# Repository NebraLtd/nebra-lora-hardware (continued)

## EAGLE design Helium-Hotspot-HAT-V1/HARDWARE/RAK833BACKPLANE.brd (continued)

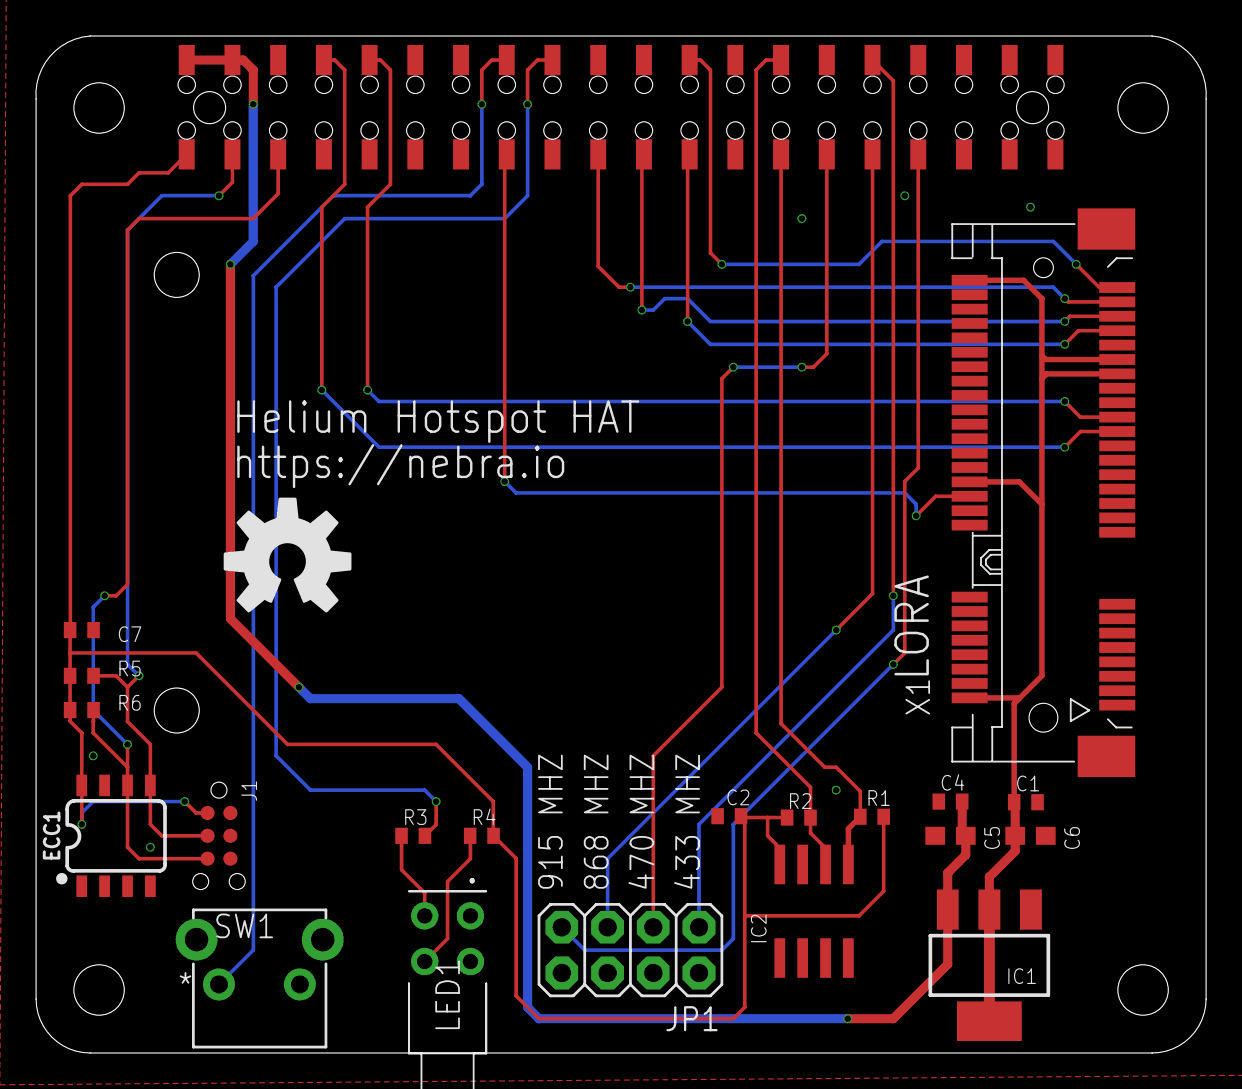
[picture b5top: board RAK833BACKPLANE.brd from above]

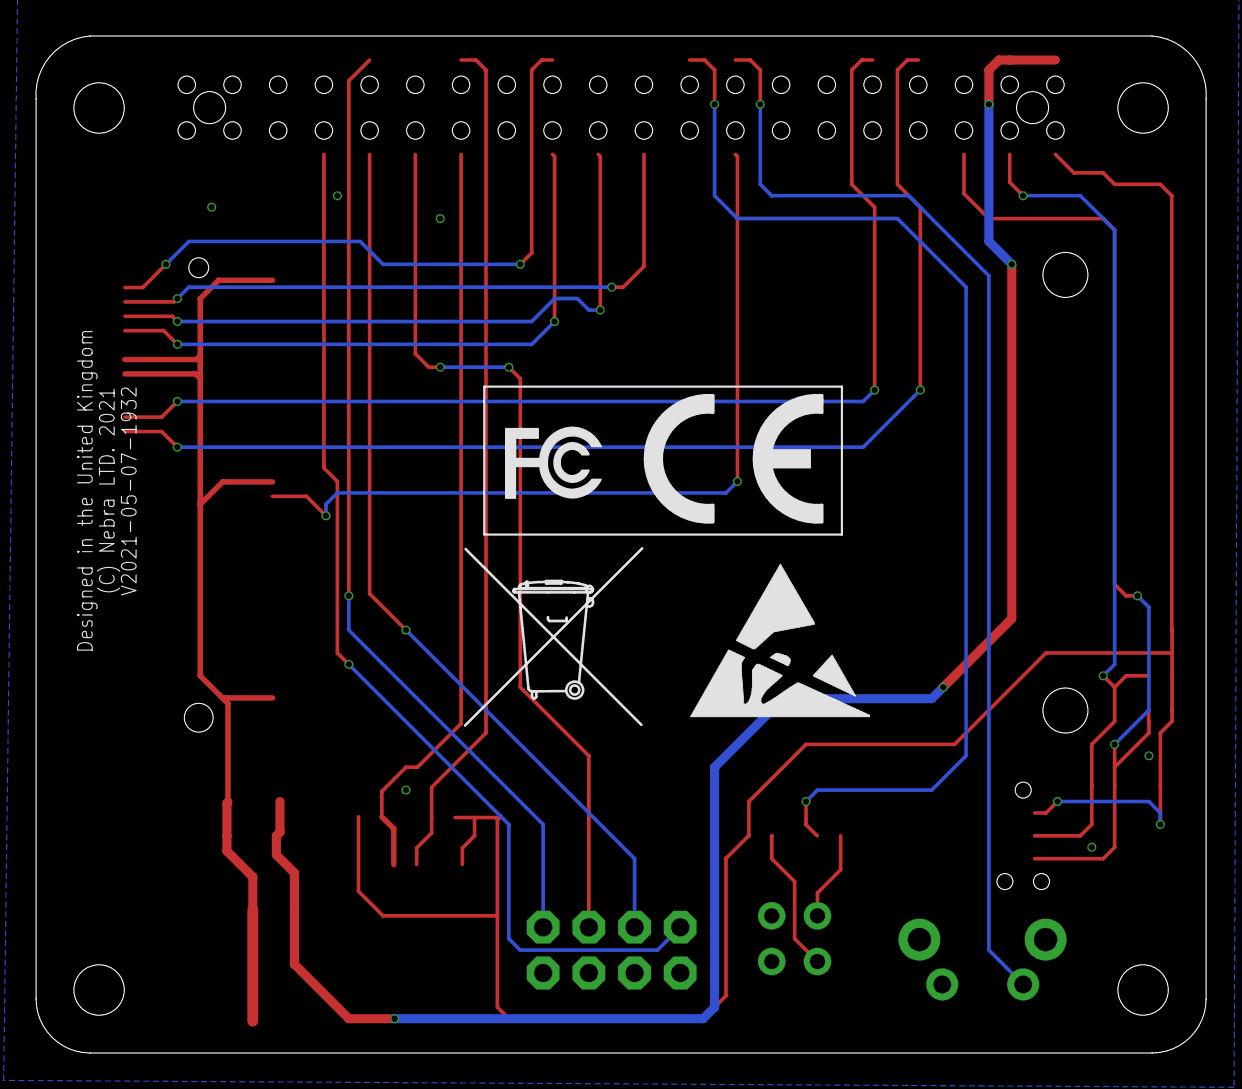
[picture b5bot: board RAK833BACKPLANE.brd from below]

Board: 2 copper layers, 65.0 x 56.5 mm, 26 parts (4 on the bottom side), 23 nets.

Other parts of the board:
U$1: TONNE_10.00
U$3: ESD_10.00
U$4: CE_7.3MM
U$5: FCC_20X8.35MM
U$6: OSHW-LOGO-L

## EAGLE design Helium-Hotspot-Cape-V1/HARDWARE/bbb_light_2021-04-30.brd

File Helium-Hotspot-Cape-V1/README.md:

# Nebra Light Hotspot Beaglebone Black Cape

The Nebra Helium Hotspot BBB Cape is designed for the new generation of helium Light Hotspots.

It features space for the Radio Module, a button & two LEDs. Along with an EEPROM to store Beaglebone Cape data and a ATECC to comply with Helium Hotspot Requirements.

# DIY Note

Please note, while you are able to build a DIY option of this board it will not earn HNT unless the ECC is programmed by an authorised Helium Maker.

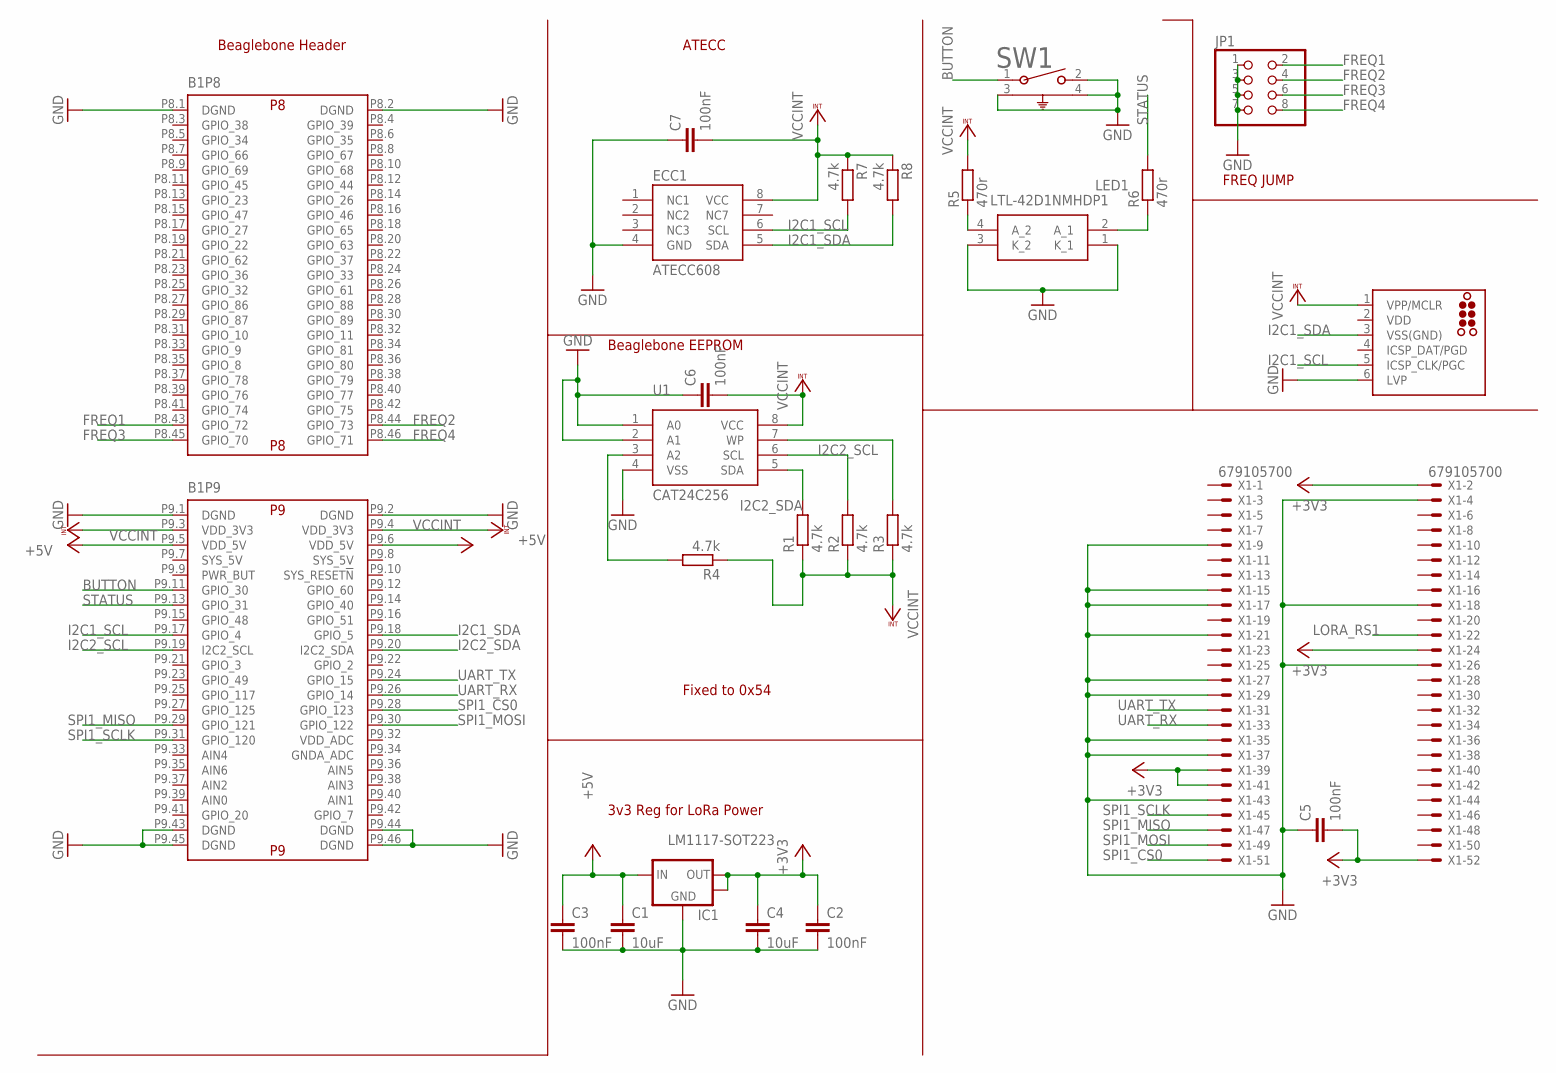
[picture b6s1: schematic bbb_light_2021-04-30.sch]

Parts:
B1: SPARKFUN_BEAGLE_BONE_BLACK_CAPE; BEAGLE_BONE_BLACK_CAPE
C1, C4: 10uF; C0603
C2, C3, C5, C6, C7: 100nF; C0603
ECC1: ATECC608; SO08
IC1: LM1117-SOT223; SOT-223-3
J1: TC2030-MCP-NL
JP1: PINHD-2X4; 2X04
LED1: LTL-42D1NMHDP1; LTL42D1NMHDP1
R1, R2, R3, R4, R7, R8: 4.7k; R0603
R5, R6: 470r; R0603
SW1: 1825027-8; SW2_1825027-C_TEC
U1: CAT24C256; SOIC8
X1: 679105700

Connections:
+3V3: C2.1, C4.1, C5.2, IC1.2 (VOUT), IC1.4 (HEATSINK), X1.2, X1.24, X1.39, X1.41, X1.52
+5V: B1.P9.5 (VDD_5V), B1.P9.6 (VDD_5V), C1.1, C3.1, IC1.3 (VIN)
BUTTON: B1.P9.11 (GPIO_30), SW1.1
FREQ1: B1.P8.43 (GPIO_72), JP1.2
FREQ2: B1.P8.44 (GPIO_73), JP1.4
FREQ3: B1.P8.45 (GPIO_70), JP1.6
FREQ4: B1.P8.46 (GPIO_71), JP1.8
GND: B1.P8.1 (DGND), B1.P8.2 (DGND), B1.P9.1 (DGND), B1.P9.2 (DGND), B1.P9.43 (DGND), B1.P9.44 (DGND), B1.P9.45 (DGND), B1.P9.46 (DGND), C1.2, C2.2, C3.2, C4.2, C5.1, C6.1, C7.1, ECC1.4 (GND), IC1.1 (GND), J1.6 (LVP), JP1.1, JP1.3, JP1.5, JP1.7, LED1.1 (K_1), LED1.3 (K_2), SW1.2, SW1.3, SW1.4, U1.1 (A0), U1.2 (A1), U1.4 (VSS), X1.4, X1.9, X1.15, X1.17, X1.18, X1.21, X1.26, X1.27, X1.29, X1.35, X1.37, X1.43
I2C1_SCL: B1.P9.17 (GPIO_4), ECC1.6 (SCL), J1.5 (ICSP_CLK/PGC), R7.2
I2C1_SDA: B1.P9.18 (GPIO_5), ECC1.5 (SDA), J1.3 (VSS(GND)), R8.2
I2C2_SCL: B1.P9.19 (I2C2_SCL), R2.2, U1.6 (SCL)
I2C2_SDA: B1.P9.20 (I2C2_SDA), R1.2, U1.5 (SDA)
LORA_RS1: X1.22
unnamed: R3.2, U1.7 (WP)
unnamed: R4.2, U1.3 (A2)
unnamed: LED1.4 (A_2), R5.1
unnamed: LED1.2 (A_1), R6.1
SPI1_CS0: B1.P9.28 (GPIO_123), X1.51
SPI1_MISO: B1.P9.29 (GPIO_121), X1.47
SPI1_MOSI: B1.P9.30 (GPIO_122), X1.49
SPI1_SCLK: B1.P9.31 (GPIO_120), X1.45
STATUS: B1.P9.13 (GPIO_31), R6.2
UART_RX: B1.P9.26 (GPIO_14), X1.33
UART_TX: B1.P9.24 (GPIO_15), X1.31
VCCINT: B1.P9.3 (VDD_3V3), B1.P9.4 (VDD_3V3), C6.2, C7.2, ECC1.8 (VCC), J1.1 (VPP/MCLR), R1.1, R2.1, R3.1, R4.1, R5.2, R7.1, R8.1, U1.8 (VCC)
VDD: J1.2 (VDD)

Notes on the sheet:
3v3 Reg for LoRa Power
Beaglebone Header
Beaglebone EEPROM
Fixed to 0x54
ATECC
FREQ JUMP

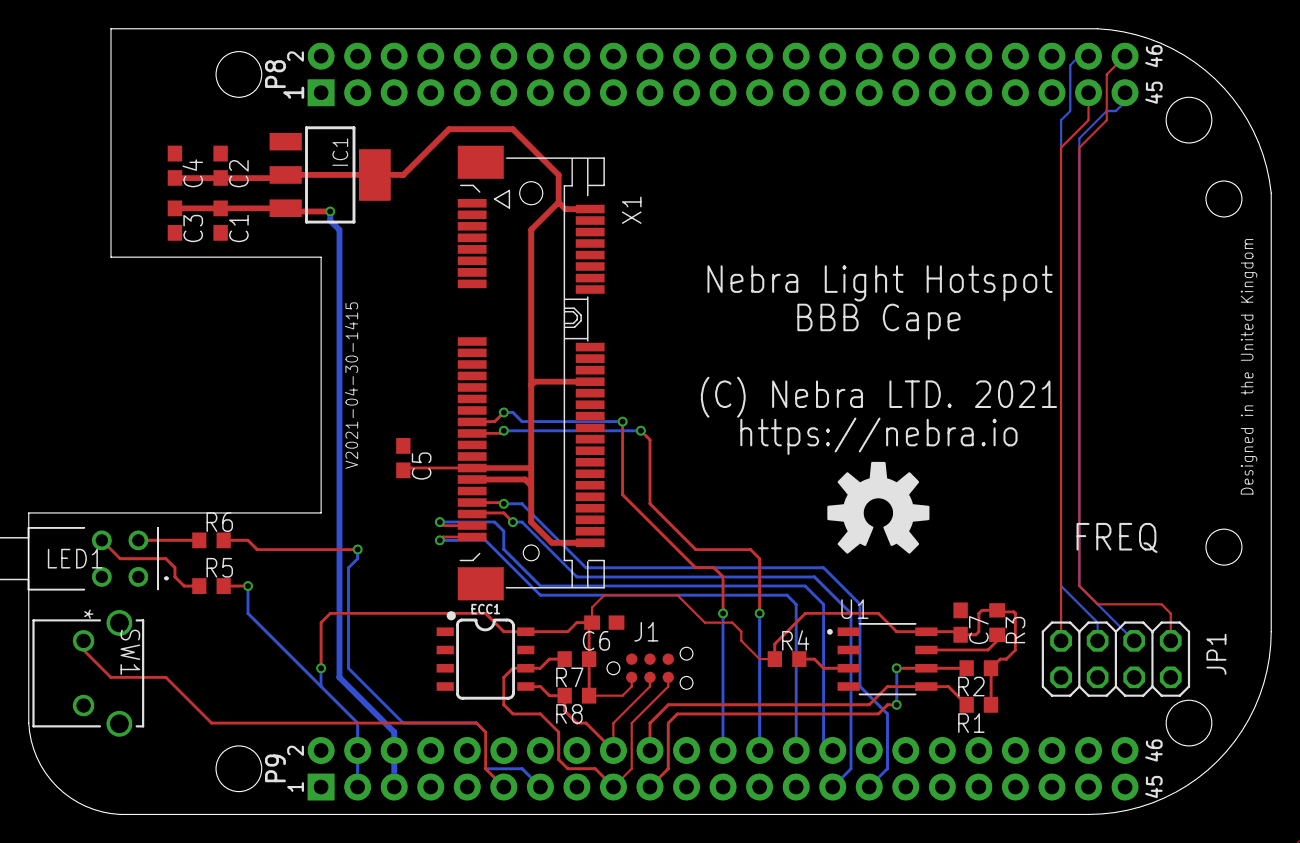
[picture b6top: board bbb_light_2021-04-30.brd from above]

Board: 2 copper layers, 86.4 x 54.6 mm, 25 parts (0 on the bottom side), 24 nets.

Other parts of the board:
U$1: OSHW-LOGO-L

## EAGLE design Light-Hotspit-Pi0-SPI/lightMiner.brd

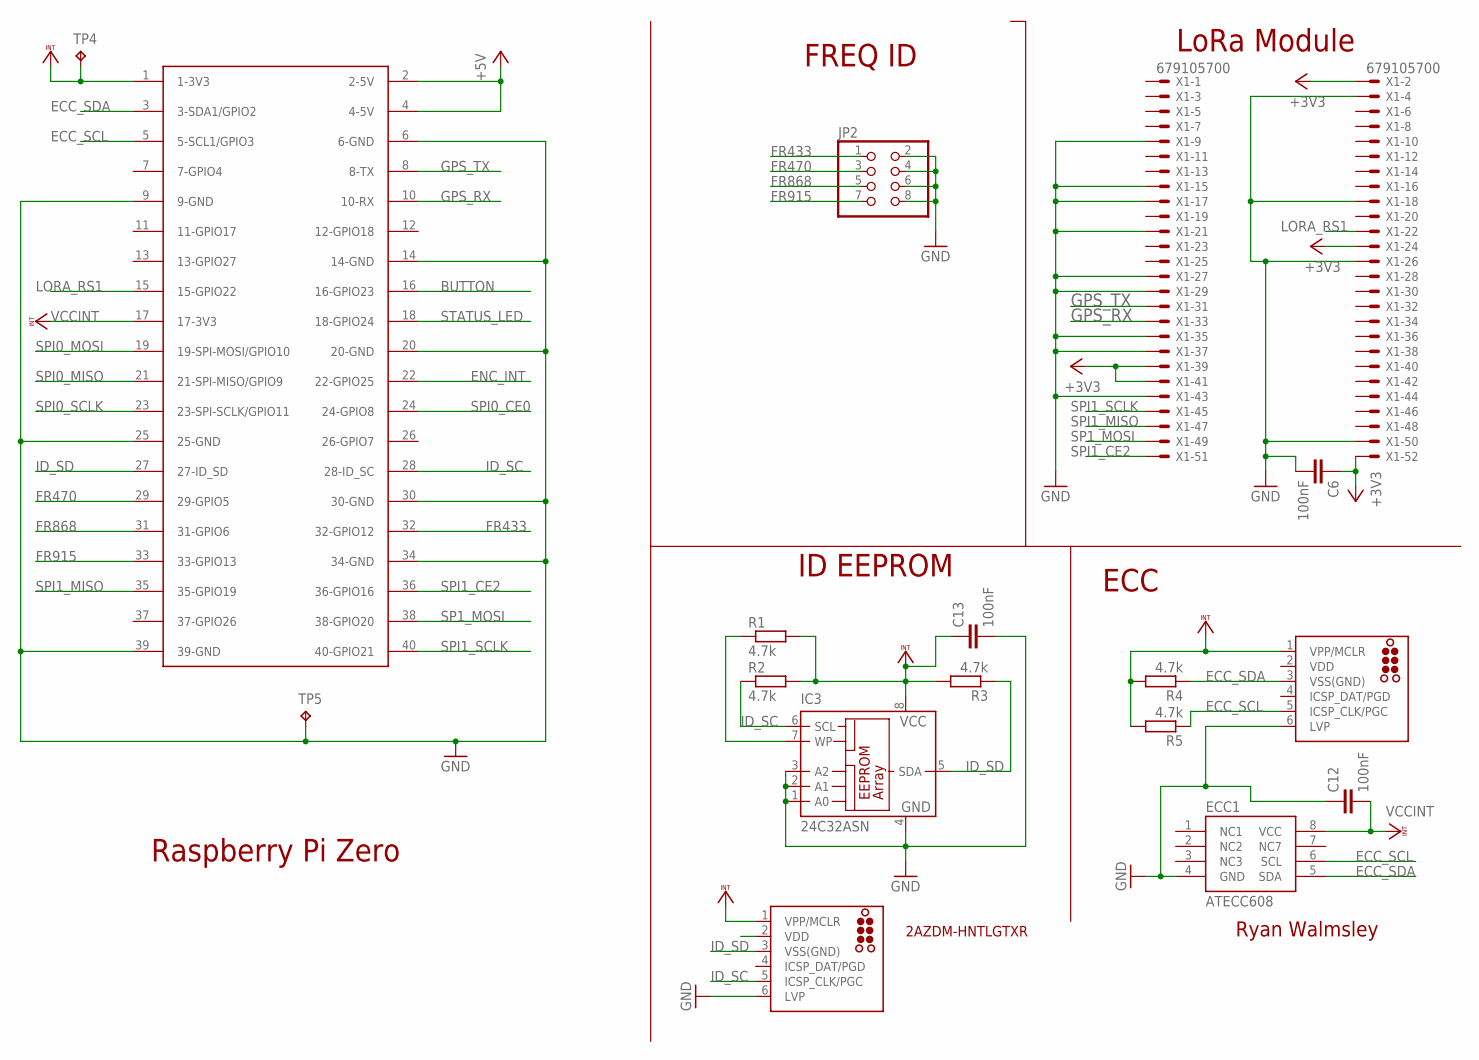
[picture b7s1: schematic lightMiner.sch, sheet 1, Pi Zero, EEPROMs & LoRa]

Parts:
C6, C12, C13: 100nF; C0603
ECC1: ATECC608; SO08
IC3: 24C32ASN; SO-08
J1, J3: TC2030-MCP-NL
JP2: PINHD-2X4; 2X04
R1, R2, R3, R4, R5: 4.7k; R0603
TP4, TP5: TPPAD1-13; P1-13
U$1: RASPBERRY-PI+PIZERO; RASPBERRY-PI-ZERO
X1: 679105700

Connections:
+3V3: C6.1, X1.2, X1.24, X1.39, X1.41, X1.52; also elsewhere on the board
+5V: U$1.2 (2-5V), U$1.4 (4-5V); also elsewhere on the board
BUTTON: U$1.16 (16-GPIO23); also elsewhere on the board
ECC_SCL: ECC1.6 (SCL), J1.5 (ICSP_CLK/PGC), R5.1, U$1.5 (5-SCL1/GPIO3)
ECC_SDA: ECC1.5 (SDA), J1.3 (VSS(GND)), R4.1, U$1.3 (3-SDA1/GPIO2)
ENC_INT: U$1.22 (22-GPIO25); also elsewhere on the board
FR433: JP2.1, U$1.32 (32-GPIO12)
FR470: JP2.3, U$1.29 (29-GPIO5)
FR868: JP2.5, U$1.31 (31-GPIO6)
FR915: JP2.7, U$1.33 (33-GPIO13)
GND: C6.2, C12.1, C13.2, ECC1.4 (GND), IC3.1 (A0), IC3.2 (A1), IC3.3 (A2), IC3.4 (GND), J1.6 (LVP), J3.6 (LVP), JP2.2, JP2.4, JP2.6, JP2.8, TP5.TP, U$1.6 (6-GND), U$1.9 (9-GND), U$1.14 (14-GND), U$1.20 (20-GND), U$1.25 (25-GND), U$1.30 (30-GND), U$1.34 (34-GND), U$1.39 (39-GND), X1.4, X1.9, X1.15, X1.17, X1.18, X1.21, X1.26, X1.27, X1.29, X1.35, X1.37, X1.43, X1.50; also elsewhere on the board
GPS_RX: U$1.10 (10-RX), X1.33
GPS_TX: U$1.8 (8-TX), X1.31
ID_SC: IC3.6 (SCL), J3.5 (ICSP_CLK/PGC), R2.1, U$1.28 (28-ID_SC)
ID_SD: IC3.5 (SDA), J3.3 (VSS(GND)), R3.1, U$1.27 (27-ID_SD)
LORA_RS1: U$1.15 (15-GPIO22), X1.22
unnamed: IC3.7 (WP), R1.1
SP1_MOSI: U$1.38 (38-GPIO20), X1.49
SPI0_CE0: U$1.24 (24-GPIO8); also elsewhere on the board
SPI0_MISO: U$1.21 (21-SPI-MISO/GPIO9); also elsewhere on the board
SPI0_MOSI: U$1.19 (19-SPI-MOSI/GPIO10); also elsewhere on the board
SPI0_SCLK: U$1.23 (23-SPI-SCLK/GPIO11); also elsewhere on the board
SPI1_CE2: U$1.36 (36-GPIO16), X1.51
SPI1_MISO: U$1.35 (35-GPIO19), X1.47
SPI1_SCLK: U$1.40 (40-GPIO21), X1.45
STATUS_LED: U$1.18 (18-GPIO24); also elsewhere on the board
VCCINT: C12.2, C13.1, ECC1.8 (VCC), IC3.8 (VCC), J1.1 (VPP/MCLR), J3.1 (VPP/MCLR), R1.2, R2.2, R3.2, R4.2, R5.2, TP4.TP, U$1.1 (1-3V3), U$1.17 (17-3V3)
VDD: J1.2 (VDD)

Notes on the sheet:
Raspberry Pi Zero
LoRa Module
ID EEPROM
ECC
FREQ ID
Ryan Walmsley
2AZDM-HNTLGTXR

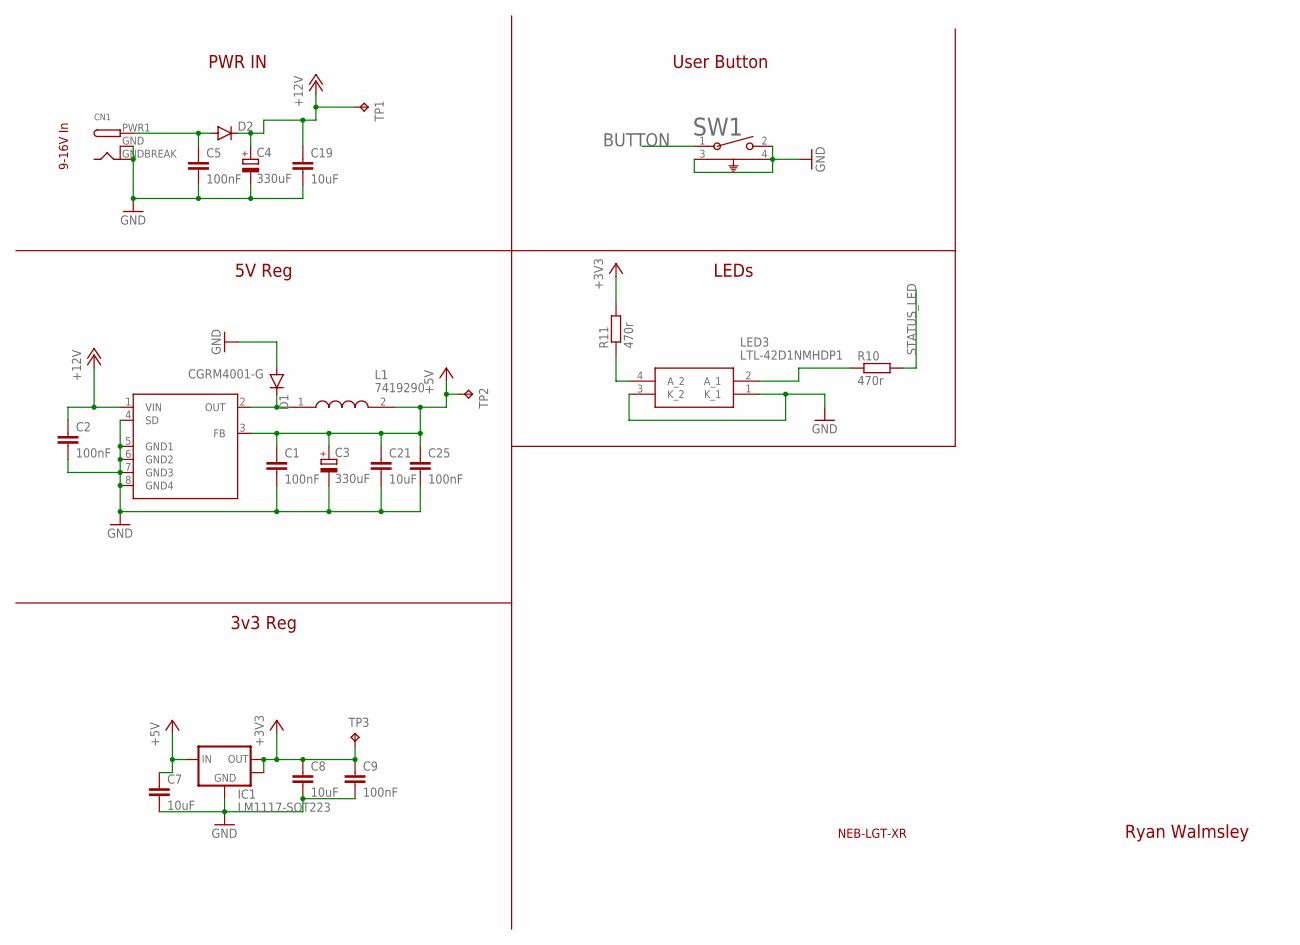
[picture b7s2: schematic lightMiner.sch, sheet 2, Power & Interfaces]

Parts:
C1, C2, C5, C9, C25: 100nF; C0603
C3, C4: 330uF; E5-10,5
C7, C8, C19, C21: 10uF; C0805
CN1: DCBARRELSMT; DCJACK_2MM_SMT
D1: CGRM4001-G; SOD-123_MINI-SMA
D2: DIODE-SMB; SMB
IC1: LM1117-SOT223; SOT-223-3
L1: 7419290; INDPM115100X410N
LED3: LTL-42D1NMHDP1; LTL42D1NMHDP1
R10, R11: 470r; R0603
SW1: 1825027-8; SW2_1825027-C_TEC
TP1, TP2, TP3: TPPAD1-13; P1-13
U1: AP1509; SO08

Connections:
+3V3: C8.1, C9.1, IC1.2 (VOUT), IC1.4 (HEATSINK), R11.2, TP3.TP; also elsewhere on the board
+5V: C1.1, C3.+, C7.1, C21.1, C25.1, IC1.3 (VIN), L1.2, TP2.TP, U1.3 (FB); also elsewhere on the board
+12V: C2.1, C4.+, C19.1, D2.C, TP1.TP, U1.1 (VIN)
BUTTON: SW1.1; also elsewhere on the board
GND: C1.2, C2.2, C3.-, C4.-, C5.2, C7.2, C8.2, C9.2, C19.2, C21.2, C25.2, CN1.GND (GNDBREAK), CN1.GNDBREAK (GND), D1.A, IC1.1 (GND), LED3.1 (K_1), LED3.3 (K_2), SW1.2, SW1.3, SW1.4, U1.4 (SD), U1.5 (GND1), U1.6 (GND2), U1.7 (GND3), U1.8 (GND4); also elsewhere on the board
unnamed: C5.1, CN1.PWR1 (PWR), D2.A
unnamed: LED3.4 (A_2), R11.1
unnamed: LED3.2 (A_1), R10.1
unnamed: D1.C, L1.1, U1.2 (OUT)
STATUS_LED: R10.2; also elsewhere on the board

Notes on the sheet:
9-16V In
PWR IN
5V Reg
3v3 Reg
User Button
LEDs
Ryan Walmsley
NEB-LGT-XR

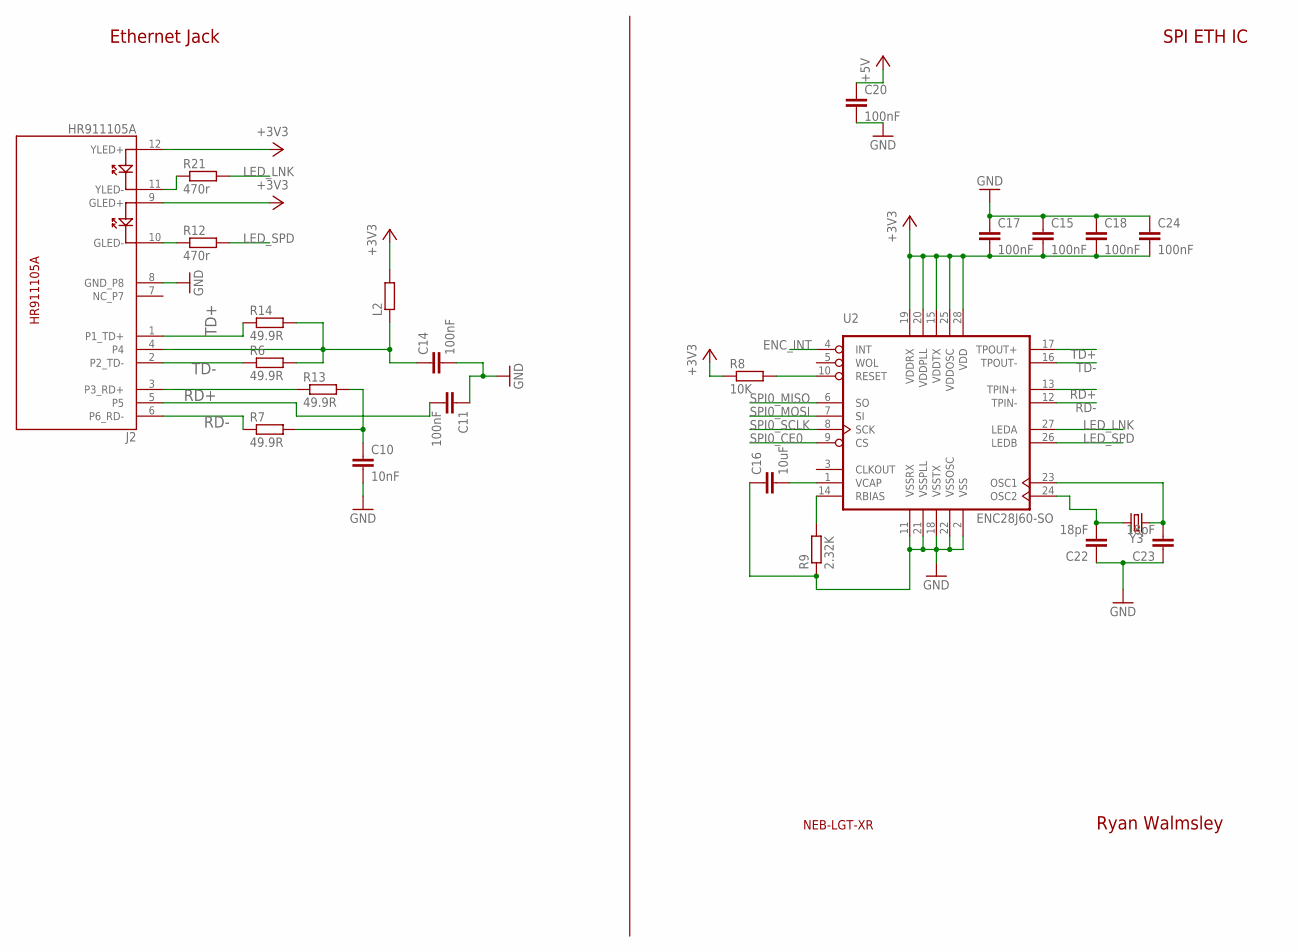
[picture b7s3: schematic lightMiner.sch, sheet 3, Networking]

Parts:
C10: 10nF; C0603
C11, C14, C15, C17, C18, C20, C24: 100nF; C0603
C16: 10uF; C0805
C22, C23: 18pF; C0603
J2: HR911105A
L2: R-EU_R0603; R0603
R6, R7, R13, R14: 49.9R; R0603
R8: 10K; R0603
R9: 2.32K; R0603
R12, R21: 470r; R0603
U2: ENC28J60-SO; SO28W
Y3: 25Mhz; HC49UP

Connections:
+3V3: C15.2, C17.2, C18.2, C24.2, J2.9 (GLED+), J2.12 (YLED+), L2.2, R8.1, U2.15 (VDDTX), U2.19 (VDDRX), U2.20 (VDDPLL), U2.25 (VDDOSC), U2.28 (VDD); also elsewhere on the board
+5V: C20.1; also elsewhere on the board
ENC_INT: U2.4 (INT); also elsewhere on the board
GND: C10.2, C11.1, C14.2, C15.1, C16.1, C17.1, C18.1, C20.2, C22.1, C23.1, C24.1, J2.8 (GND_P8), R9.1, U2.2 (VSS), U2.11 (VSSRX), U2.18 (VSSTX), U2.21 (VSSPLL), U2.22 (VSSOSC); also elsewhere on the board
LED_LNK: R21.2, U2.27 (LEDA)
LED_SPD: R12.2, U2.26 (LEDB)
unnamed: J2.11 (YLED-), R21.1
unnamed: C10.1, R7.2, R13.2
unnamed: J2.10 (GLED-), R12.1
unnamed: C16.2, U2.1 (VCAP)
unnamed: C11.2, J2.5
unnamed: C22.2, U2.24 (OSC2), Y3.2
unnamed: C14.1, J2.4, L2.1, R6.2, R14.2
unnamed: R8.2, U2.10 (RESET)
unnamed: R9.2, U2.14 (RBIAS)
unnamed: C23.2, U2.23 (OSC1), Y3.1
RD+: J2.3 (P3_RD+), R13.1, U2.13 (TPIN+)
RD-: J2.6 (P6_RD-), R7.1, U2.12 (TPIN-)
SPI0_CE0: U2.9 (CS); also elsewhere on the board
SPI0_MISO: U2.6 (SO); also elsewhere on the board
SPI0_MOSI: U2.7 (SI); also elsewhere on the board
SPI0_SCLK: U2.8 (SCK); also elsewhere on the board
TD+: J2.1 (P1_TD+), R14.1, U2.17 (TPOUT+)
TD-: J2.2 (P2_TD-), R6.1, U2.16 (TPOUT-)

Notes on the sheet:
Ryan Walmsley
Ethernet Jack
SPI ETH IC
NEB-LGT-XR

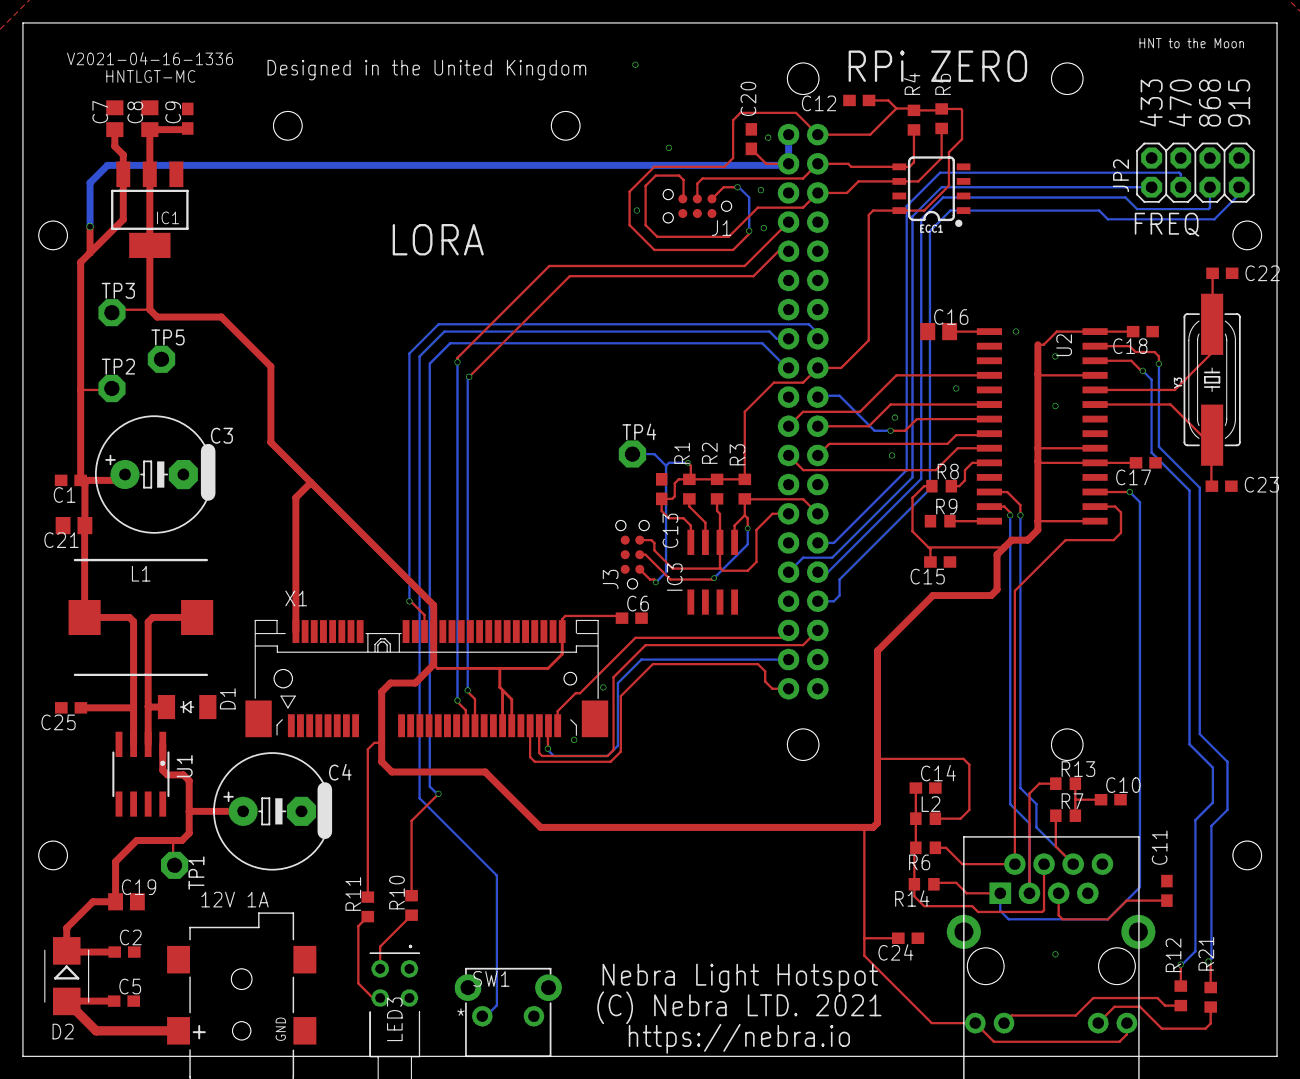
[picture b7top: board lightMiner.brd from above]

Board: 2 copper layers, 109.2 x 90.0 mm, 64 parts (1 on the bottom side), 48 nets.

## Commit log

2021-05-14 Create Layout.
2021-05-14 Add in licenses.
2021-05-14 Add license information.
2021-05-14 Add Beaglebone Cape Files
2021-05-14 Shuffle parts around for the cape.
2021-05-14 Add Hotspot HAT Files
2021-05-14 Add readme details.
2021-05-14 Add ECC USB Hub Files
2021-05-14 Add daughterboard gerbers
2021-05-14 Adds Pinout File
2021-05-14 Add Outdoor Mainboard Files
2021-05-14 Add smart indoor files.
2021-05-14 Add ECC Key gerbers
2021-05-25 Change PDFS
2021-06-17 Update schematic for indoor mainboard to not be mirrored.
2021-06-17 Fix mirroring of outdoor mainboard.
2021-06-17 Update daughterboard schematic to not be mirrored.
2021-06-17 Replace ECCUSB Hub schematic with correct version.
2021-06-17 Add beaglebone cape schematic.
2021-06-17 Update hotspot hat schematic.
2021-06-17 Un mirror front.
2021-07-20 Add in Light Hotspot Pi 0 SPI Files
2021-07-30 update folder name
    correct typo in folder name
2021-07-30 typo fix
